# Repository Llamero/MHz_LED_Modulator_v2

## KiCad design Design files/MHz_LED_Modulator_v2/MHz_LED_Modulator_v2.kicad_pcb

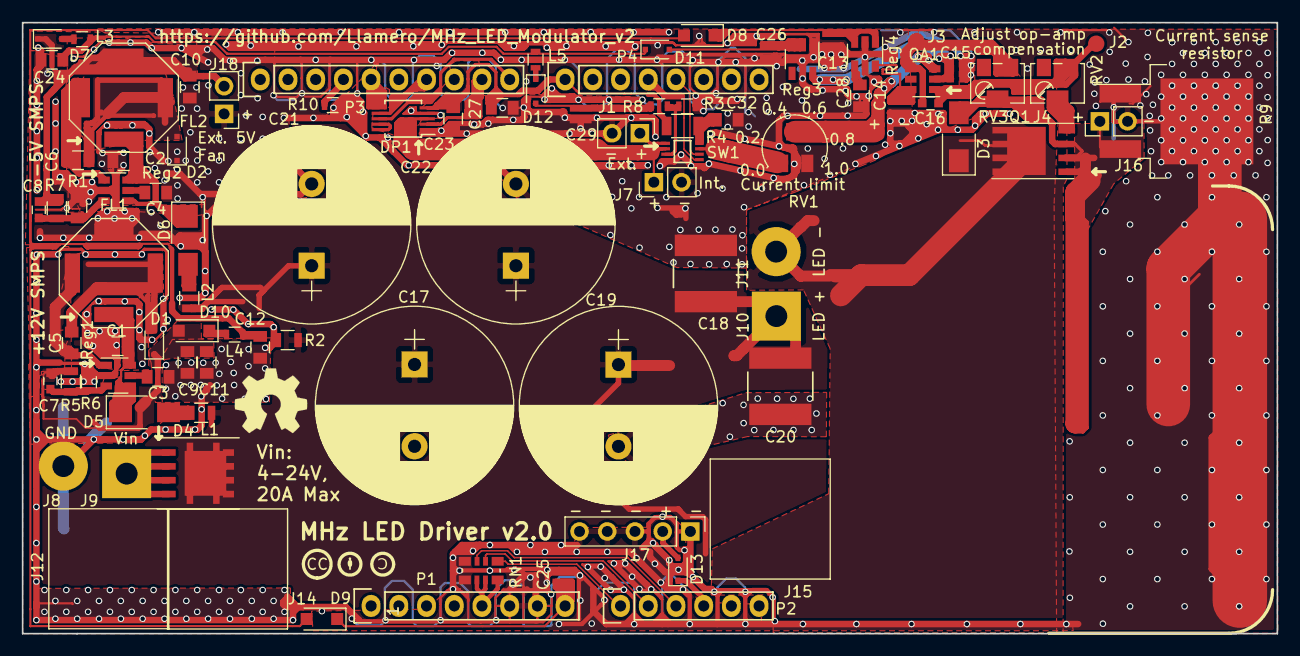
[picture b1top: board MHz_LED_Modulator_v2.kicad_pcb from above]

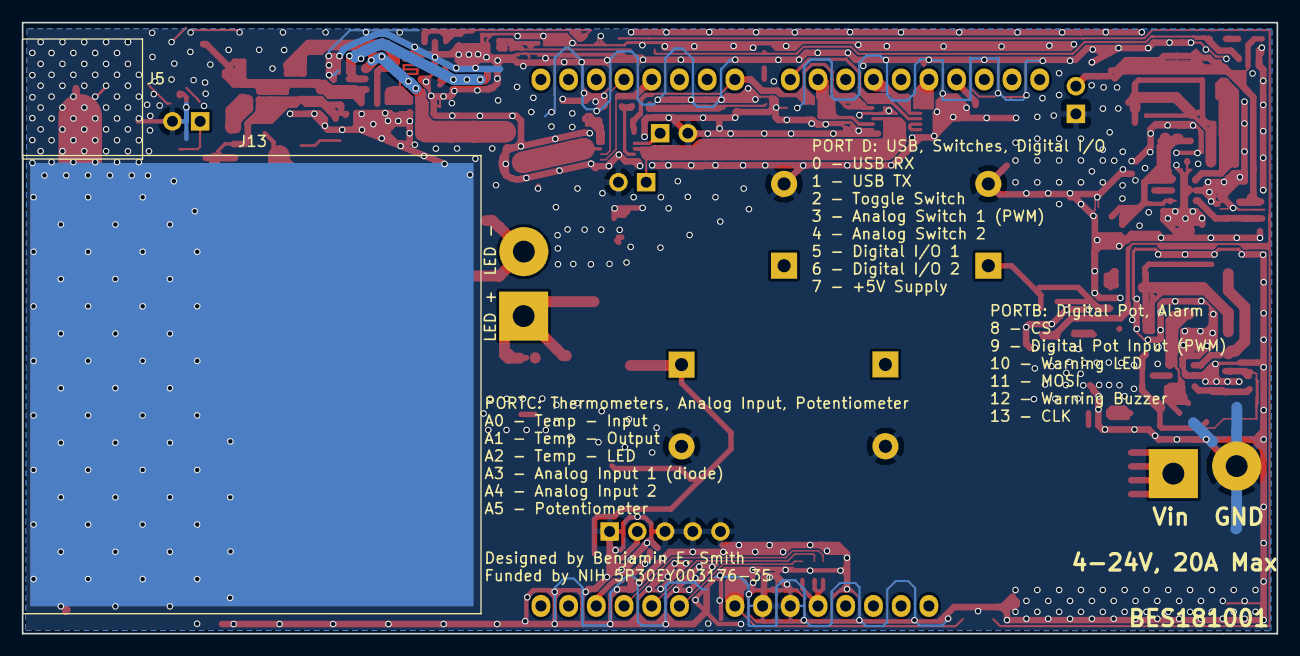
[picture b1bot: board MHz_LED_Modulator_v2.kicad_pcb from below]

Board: 2 copper layers, 115.0 x 56.0 mm, 98 parts (2 on the bottom side), 55 nets.

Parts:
C1, C2, C9, C10, C11, C12, C24, C27: 4.7 uF; C_0805
C3, C4, C5, C6: 1 uF; C_0805
C7, C8: 4.7 pF; C_0603
C13, C14, C15, C25, C26, C29: 2.2 uF; 0508_Capacitor
C16: 2200 pF; C_0603
C17, C19, C21, C22: 2700 uF; CP_Radial_D18.0mm_P7.50mm
C18, C20: 22 uF; 2_J-lead_stacked_cap
C23, C28, C32: 10 nF; C_0805
D1, D2: D_Schottky; D_SOD-323F
D3: D_TVS; DO-214AC
D4: D; Powerdi5060-8
D5, D6: D_Schottky; DO-214AC
D7, D11, D12: D; D_SOD-323F
D8, D9, D10: D_Schottky; D_SOD-123F
D13: D_Schottky; D_SOD-323
DP1: AD5162; MSOP-10_3x3mm_Pitch0.5mm
FL1: 4.7uH; Wurth_Coupled_Inductor
FL2: 2.7uH; Wurth_Coupled_Inductor
J1, J7, J16, J18: Conn_Coaxial; Socket_Strip_Straight_1x02_Pitch2.54mm
J2, J3, J4: TEST_1P; Measurement_Point_Round-SMD-Pad_Small
J5, J12, J14, J15: Heat_Sink; Heatsink-10x10mm-V2017B
J6: Heat_Sink; 40x40mm-heatsink_only-eighth-pad
J8, J11: TEST_1P; SolderWirePad_single_2mmDrill
J9, J10: TEST_1P; SolderWirePad_single_2mmDrill-square
J13: Heat_Sink; Heatsink-Wakefield_655-53AB_41x41mm
J17: Conn_01x05_Female; Socket_Strip_Straight_1x05_Pitch2.54mm
L1, L2: Ferrite_Bead; L_0805
L3, L4, L5: Ferrite_Bead; L_0603
OA1: LT6200-10; SOT-23-6
P1: Power; Socket_Strip_Arduino_1x08
P2: Analog; Socket_Strip_Arduino_1x06
P3: Digital; Socket_Strip_Arduino_1x10
P4: Digital; Socket_Strip_Arduino_1x08
Q1: Q_NMOS_GDS; IRFH5104_PQFN_5x6b
R1: 187k; C_0805
R2: 4.7k; R_0805
R3: 100; R_0603
R4: 0; R_1206
R5, R7: 1Meg; R_0805
R6: 154k; R_0603
R8: 1.8k; R_0603
R9: 5; Bourns_DPAK
R10: 10; R_0603
RN1: 4.7k; Resistor_Array_x4_1206
RV1: POT_TRIM; Bourns_3313J_Trimpot-compact
RV2, RV3: POT_TRIM; Potentiometer_Trimmer_Bourns_3224W
RV4: 10k; OSHW-Symbol_6.7x6mm_SilkScreen
Reg1, Reg2: LT8330; SOT-23-6
Reg3: ADP7182AUJZ-Fixed; TSOT-23-5
Reg4: LP2985-10.0; SOT-23-5
SW1: TS5A3357DCUR; 8-VFSOP
TH1: 10k; CC_silkscreen
TH2: 10k; CC_Attribution
TH3: 10k; CC_Share_alike

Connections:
10V: C14.2, OA1.6, Reg4.5
+5V: P1.5, RN1.6, RN1.7, RN1.8
-2V: C15.2, OA1.2, Reg3.5
/3(**): P4.5, SW1.6
/4: P4.4, SW1.5
/7: C23.1, C27.2, DP1.5, P4.1, R4.1
/8: DP1.8, P3.10
/9(**): DP1.2, P3.9
/11(**/MOSI): DP1.7, P3.7
/12V-SMPS: C7.2, C9.2, C11.2, D1.1, D10.2, R5.2
/13(SCK): DP1.6, P3.5
/-4V: C24.2, D11.1, L3.1, L5.1
/-5V-SMPS: C8.2, C10.2, D7.1, FL2.3, J18.2, R7.2
/A0: P2.1, RN1.1
/A1: P2.2, RN1.2
/A2: P2.3, RN1.3
/A3: D13.1, P2.4
/Input: RV1.3, SW1.7
/Vin(Arduino): C25.1, D9.1, P1.8
GND: C1.2, C2.2, C3.1, C4.1, C9.1, C10.1, C11.1, C12.1, C13.2, C14.1, C15.1, C17.2, C18.2, C19.2, C20.1, C21.2, C22.2, C23.2, C24.1, C25.2, C26.2, C27.1, C28.2, C29.1, C32.2, D2.1, DP1.1, DP1.4, FL1.3, J1.2, J5.1, J6.1, J7.2, J8.1, J13.1, J16.2, J17.1, J17.3, J17.4, J17.5, J18.1, P1.6, P1.7, R1.2, R2.1, R3.1, R6.2, R9.1, R9.2, R10.1, RN1.4, RN1.5, RV1.1, Reg1.2, Reg2.2, Reg3.1, Reg4.2, SW1.4
GND(NC): P3.4, R10.2
unnamed: C1.1, D5.1, FL1.1, Reg1.4, Reg1.6
unnamed: C2.1, D6.1, FL2.1, Reg2.4, Reg2.6
unnamed: C3.2, Reg1.5
unnamed: C4.2, Reg2.5
unnamed: C5.1, FL1.4, Reg1.1
unnamed: C5.2, D1.2, FL1.2
unnamed: C6.1, FL2.4, Reg2.1
unnamed: C6.2, D2.2, FL2.2
unnamed: C7.1, R5.1, R6.1, Reg1.3
unnamed: C8.1, R1.1, R7.1, Reg2.3
unnamed: C12.2, D8.2, D9.2, L4.1
unnamed: C13.1, D8.1, Reg4.1, Reg4.3
unnamed: C16.1, J3.1, OA1.4, RV3.1
unnamed: C16.2, J2.1, OA1.1, RV2.1
unnamed: C26.1, D11.2, Reg3.2, Reg3.3
unnamed: C28.1, Reg4.4
unnamed: C29.2, D12.2, R8.1
unnamed: C32.1, R4.2, SW1.8
unnamed: D3.1, J11.1, Q1.2
unnamed: D3.2, J16.1, Q1.3, R9.3, RV3.2
unnamed: D4.2, J9.1
unnamed: D5.2, L1.1
unnamed: D6.2, L2.1
unnamed: D7.2, L3.2
unnamed: D10.1, L4.2
unnamed: D12.1, L5.2
unnamed: D13.2, J17.2
unnamed: DP1.3, J7.1, SW1.2
unnamed: DP1.9, DP1.10
unnamed: J1.1, SW1.1
unnamed: J4.1, Q1.1, RV2.2
unnamed: OA1.3, RV1.2
unnamed: R3.2, R8.2, SW1.3
Vin: C17.1, C18.1, C19.1, C20.2, C21.1, C22.1, D4.1, J10.1, J12.1, J14.1, J15.1, L1.2, L2.2, R2.2

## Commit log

2018-08-08 :confetti_ball: Added .gitattributes & .gitignore files
2018-08-08 Initialize
2018-08-08 Create LICENSE
2018-08-09 Knob GUI added
2018-08-09 Knob GUI centered
2018-08-09 Rotating knob
2018-08-09 Fixed RotatePanel class so that is doesn't return errors into the Design Mode GUI causing it to become unusable. The solution was to check if an image is null, and if so load a dummy image. The solut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
2018-08-09 Knob is now inititialized in design mode rather than default rectangle, and knob is centered.
2018-08-09 3 offset added to X translation to keep knob centered in dial scale during rotation
2018-08-09 -1 offset added to Y translation to keep knob centered in dial scale during rotation
2018-08-09 Main class added to POM to make JAR executable. GUI class is temporarily set as main class for now.
2018-08-09 Slider ofr knob with formatted percentage label
2018-08-09 Antialias knob rotation to smooth edges
2018-08-10 Sends byte to Arduino and then builds GUI
2018-08-11 Temporarily commented out serial
2018-08-23 Knob graphic is circularized. Arduino handshake and multi-arduino ID is implemented and runs on thread separate from GUI.
2018-08-23 GUI is updated based on handshake status.
2018-08-24 Added radio menu option to choose which device to connect to.
2018-08-24 Cleaned up code removing arduinoPort specific SerialPort[] ,and instead just directly using serialPorts[]
2018-08-24 Added comments
2018-08-25 Switch to Eclipse
2018-08-25 Remove Netbeans version
2018-08-25 Cleaning up repo
2018-08-25 test
2018-08-25 Functions as standalone jar
2018-08-25 Removed unused class
2018-08-25 Fixed progress bar
2018-08-25 Fixed problem with JFrame not closing if no COM ports were found
2018-08-29 Added packet streaming for more reliable serial initialization
2018-08-30 All packets in buffer are parsed, rather than just first one.
    All valid packets are parsed, only one response byte is sent for one or
    more valid packets in buffer. On initialization, buffer is searched for
    only ID packets, all other packets are ignored.
2018-08-30 Finished temperature streaming
    The program can now parse temperature streams, and then calculate the
    temperature based off of the given beta value. The GUI has also been
    de-jittered to remove twiching temperature responses due to ADC steps
    that are larger than 1oC.
2018-08-30 Add backup of test programs
2018-08-30 test commit
2018-08-30 finish test
2018-08-30 updated jar
2018-09-05 Framework for MVC
2018-09-05 Further progress on MVC model
2018-09-06 Resolved issue where Eclipse and the compiled executable JAR look in different directories for the images. Therefore, used a con
2018-09-06 Serial is working
2018-09-06 Reads and writes to Arduino!
2018-09-06 extra
2018-09-06 GUI now loads prefs and refreshes display to go to default positions.
2018-09-14 Add serial comm via interrupts
    Arduino will now incrementally check its status, send info to gui, and
    rec bytes in single increments to reduce jitter in code timing. Code
    can use interrupts in normal operation (using 1 ms clock) or use mirror
    sync as interrupt clock (i.e. check right before next sync wait.
2018-09-15 Added initialization flow chart
2018-09-15 Initialization flow chart for both driver and GUI
2018-09-15 Initialize draft complete - untested
    Circular rx buffer is implmented, interrupt events set event flag rather
    than directly calling function (resolves issues with setting registers
    on the Arduino), failSafe now uses interrupts rather than calls to check
    status, new header structure (NEED TO UPDATE IN GUI), packet size is now
    full packet size, and check sum is sum of only data (solves issue of
    checksum possibly going to 0),.
2018-09-15 Added backbone for option of adjusting alarm volume
2018-09-15 Added backbone implementation for adjusting volume via knob
2018-09-24 parseSerial updated to use circular buffer - untested
2018-10-15 Fixed circular buffer to use real mod and catch packets at very end of buffer
2018-10-16 Fixed check status interupt
    Calling checkStatus in interrupt was jamming scipts that came after, so checkStatus now only flips a variable flag, allowing calls to that flag to activate check status.
2018-10-16 During initialization, driver is told to hold rather than continue initialization.
2018-10-16 Disconnect funciton is cleaned up, and Arduino will now either retrieve setup (on connect) or go into standby (on initialize)
2018-10-16 Hand shake is successful GUI sends prefs to driver, and driver checks validity and replies with a the same packet.
2018-10-16 Arduino with debugged handshake
2018-10-16 Fixed bug where ID would get scrambled if other data was in buffer.
2018-10-17 Update Arduino Test Programs/Receive_setup_from_GUI/Receive_setup_from_GUI.ino
    Fixed serial reading during check status
    The driver tx would hang on disconnect, likely because the port it was writing too was no longer available. The problem was that the Arduino would need over a second, after the port was closed to par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
2018-10-17 Update Arduino Test Programs/Receive_setup_from_GUI/Receive_setup_from_GUI.ino
    Device now successfully goes into standby when disconnected.
2018-10-17 Fixed array copying issue When arrays are set equal, their references are equal - i.e. they become the same object and changes to one change the other. Instead, to make and independent copy, the elem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
2018-10-17 Fixed Fault state
2018-10-17 syntax
2018-10-17 Removed initial ADC reads as they do not help to reduce initial overshoot on A0
2018-10-18 Status is updated while connection is made Connection sequence is also noe performed on a swingworker backgorund thread.
2018-10-18 Temp panel turns orange then red when overheating
2018-10-18 Arduino now has digital confocal sync with 100ns jitter
2018-10-20 Analog sync added - 8us jitter
2018-10-20 Manual mode with toggle introduced
2018-10-23 Arduino now does dummy status checks on initialize to stabilize ADCs
2018-10-25 Fan min PWM added as setup option
    min PWM needed to start fan.
2020-05-21 Add design files
2020-07-23 Add schematic
2023-10-19 Upload both sync programs
